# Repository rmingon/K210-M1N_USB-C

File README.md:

# K210-M1N USB-C Adapter

This repository contains the KiCad 9 project for a compact adapter board that breaks out the **Kendryte K210 M1n** M.2 (Key‑B) module to USB and a minimal set of GPIOs. The board’s USB‑C port is intended primarily for power and UART-based programming through an onboard CH340C USB–serial bridge.

## Hardware Overview

- **Form factor** – Single board implementing the Amphenol MDT320B03001 Key‑B M.2 socket on the top side and a USB‑C receptacle on the edge for direct plug-in to a host.
- **Power** – USB VBUS feeds the CH340C (`+5V`) and is decoupled locally (C9). The board relies on the M1n module’s onboard regulators for `+3.3V` and `+1V8`.
- **USB–UART** – CH340C in SOIC‑16 package with `D+`/`D-` routed to the USB‑C connector and a BOOT/RESET autoprogramming network (R7 to BOOT, R8 to RESET).
- **Status LEDs** – Two LEDs (D1/D2) with current-limiting resistors (R3/R4) monitor `+5V` and `VBUS`.
- **Breakout signals** – Key M.2 pins (IO, SPI0, DVP, etc.) are accessible via the module connector. The schematic uses global labels (`IO4`, `IO5`, …) matching Kendryte’s numbering.

### Board visuals

## Programming Workflow

- The CH340C exposes a UART for flashing firmware onto the K210 module.
- `~RTS` is routed through R8 to the `RST` net (M.2 pad 10), while `~DTR` drives the `BOOT` net (M.2 pad 53) via R7 to automate the boot sequence used by Kendryte tooling.
- Connect the USB‑C port to your host PC, install CH340 drivers if needed, and use Kendryte’s flashing tools over the enumerated serial port.

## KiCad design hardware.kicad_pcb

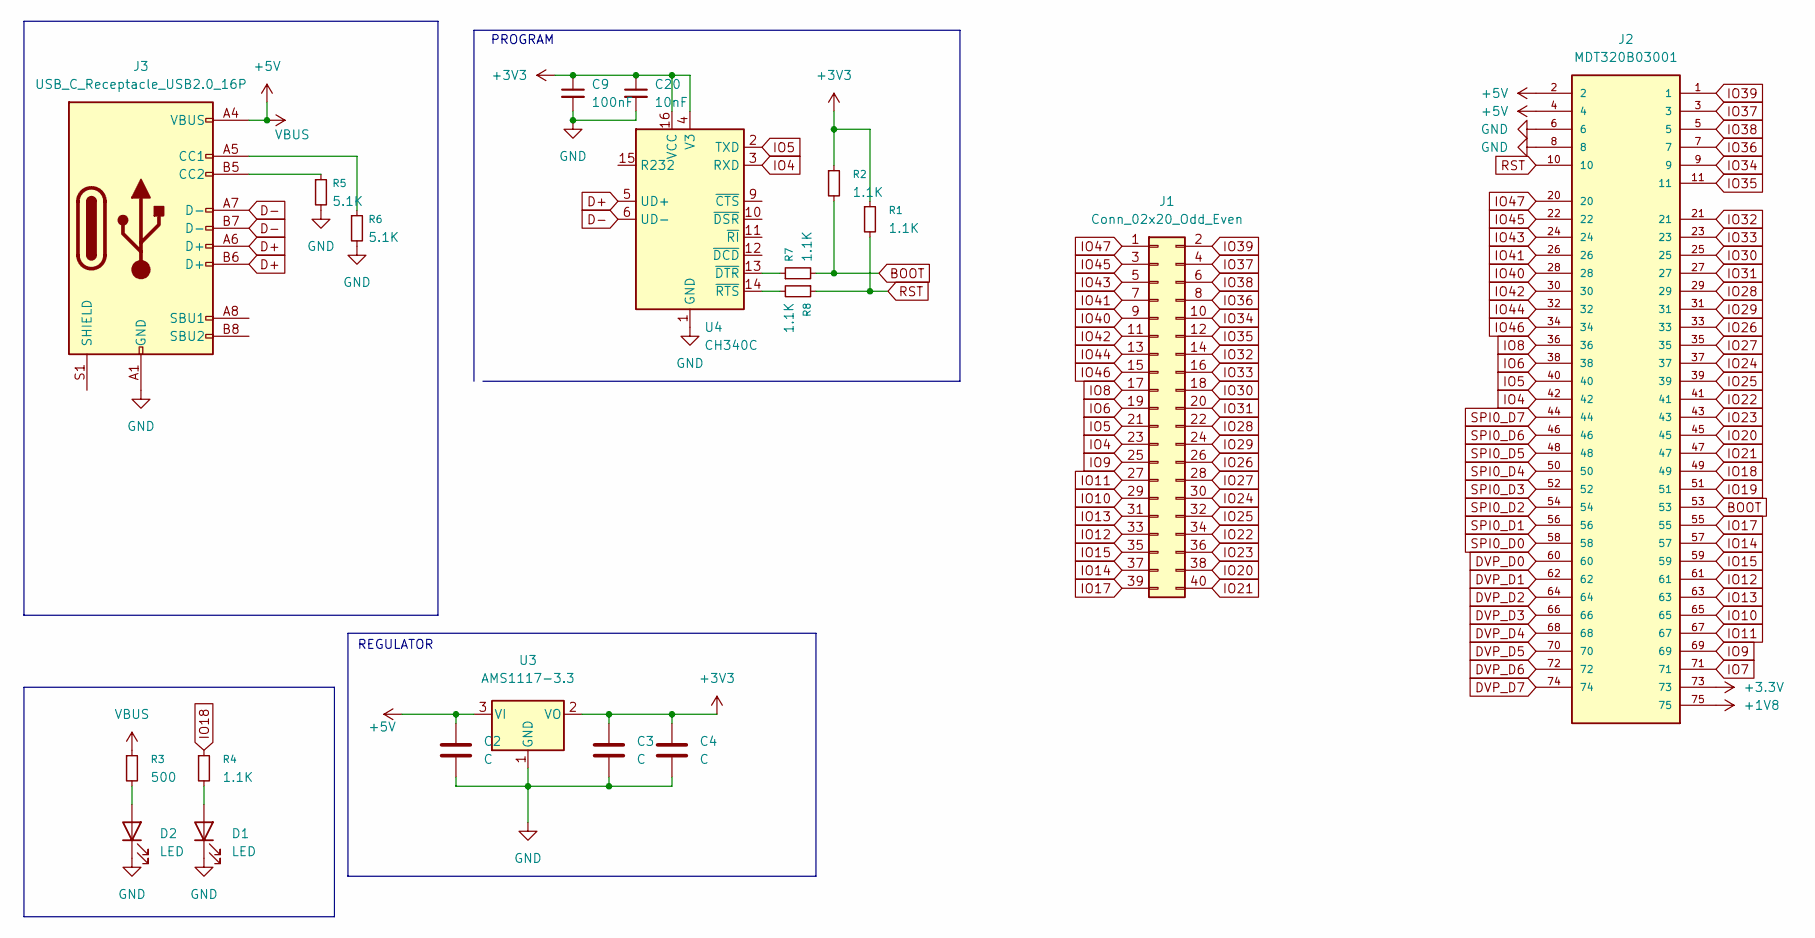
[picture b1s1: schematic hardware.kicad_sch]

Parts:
C2, C4: C; C_0603_1608Metric; LCSC C30926
C3: C; C_0603_1608Metric; LCSC C19702
C9: 100nF; C_0603_1608Metric
C20: 10nF; C_0603_1608Metric
D1, D2: LED; LED_0603_1608Metric
J1: Conn_02x20_Odd_Even; IDC-Header_2x20_P2.54mm_Horizontal
J2: MDT320B03001; AMPHENOL_MDT320B03001; PARTREV 4
J3: USB_C_Receptacle_USB2.0_16P
R1, R2, R4, R7, R8: 1.1K; R_0603_1608Metric
R3: 500; R_0603_1608Metric
R5, R6: 5.1K; R_0603_1608Metric
U3: AMS1117-3.3; SOT-223-3_TabPin2; LCSC C6186
U4: CH340C; SOIC-16_3.9x9.9mm_P1.27mm

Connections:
+1V8: J2.75
+3.3V: J2.73
+3V3: C3.1, C4.1, C9.1, C20.1, R1.1, R2.1, U3.2 (VO), U4.4 (V3), U4.16 (VCC)
+5V: C2.1, J2.2, J2.4, J3.A4 (VBUS), J3.A9 (VBUS), J3.B4 (VBUS), J3.B9 (VBUS), R3.1, U3.3 (VI)
BOOT: J2.53, R2.2, R7.2
D+: J3.A6 (D+), J3.B6 (D+), U4.5 (UD+)
D-: J3.A7 (D-), J3.B7 (D-), U4.6 (UD-)
DVP_D0: J2.60
DVP_D1: J2.62
DVP_D2: J2.64
DVP_D3: J2.66
DVP_D4: J2.68
DVP_D5: J2.70
DVP_D6: J2.72
DVP_D7: J2.74
GND: C2.2, C3.2, C4.2, C9.2, C20.2, D1.1 (K), D2.1 (K), J2.6, J2.8, J3.A1 (GND), J3.A12 (GND), J3.B1 (GND), J3.B12 (GND), R5.2, R6.2, U3.1 (GND), U4.1 (GND)
IO4: J1.23, J2.42, U4.3 (RXD)
IO5: J1.21, J2.40, U4.2 (TXD)
IO6: J1.19, J2.38
IO7: J2.71
IO8: J1.17, J2.36
IO9: J1.25, J2.69
IO10: J1.29, J2.65
IO11: J1.27, J2.67
IO12: J1.33, J2.61
IO13: J1.31, J2.63
IO14: J1.37, J2.57
IO15: J1.35, J2.59
IO17: J1.39, J2.55
IO18: J2.49, R4.1
IO19: J2.51
IO20: J1.38, J2.45
IO21: J1.40, J2.47
IO22: J1.34, J2.41
IO23: J1.36, J2.43
IO24: J1.30, J2.37
IO25: J1.32, J2.39
IO26: J1.26, J2.33
IO27: J1.28, J2.35
IO28: J1.22, J2.29
IO29: J1.24, J2.31
IO30: J1.18, J2.25
IO31: J1.20, J2.27
IO32: J1.14, J2.21
IO33: J1.16, J2.23
IO34: J1.10, J2.9
IO35: J1.12, J2.11
IO36: J1.8, J2.7
IO37: J1.4, J2.3
IO38: J1.6, J2.5
IO39: J1.2, J2.1
IO40: J1.9, J2.28
IO41: J1.7, J2.26
IO42: J1.11, J2.30
IO43: J1.5, J2.24
IO44: J1.13, J2.32
IO45: J1.3, J2.22
IO46: J1.15, J2.34
IO47: J1.1, J2.20
unnamed: D1.2 (A), R4.2
unnamed: D2.2 (A), R3.2
unnamed: J3.A5 (CC1), R6.1
unnamed: J3.B5 (CC2), R5.1
unnamed: R7.1, U4.13 (~DTR)
unnamed: R8.2, U4.14 (~RTS)
RST: J2.10, R1.2, R8.1
SPI0_D0: J2.58
SPI0_D1: J2.56
SPI0_D2: J2.54
SPI0_D3: J2.52
SPI0_D4: J2.50
SPI0_D5: J2.48
SPI0_D6: J2.46
SPI0_D7: J2.44

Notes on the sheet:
PROGRAM
REGULATOR

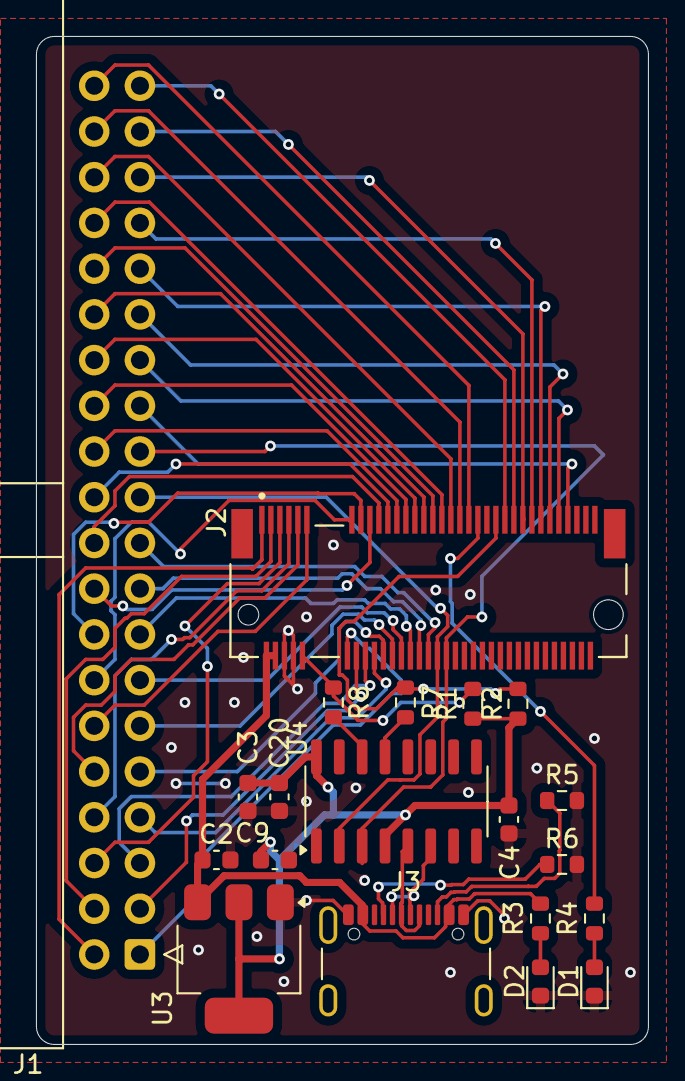
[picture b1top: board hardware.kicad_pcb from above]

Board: 2 copper layers, 34.0 x 56.0 mm, 20 parts (0 on the bottom side), 54 nets.

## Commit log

2025-11-01 add wiring + pcb
2025-11-01 add pictures
2025-11-01 switch uart wiring
2025-11-01 add readme
2025-11-06 add testing header
2025-11-06 add rst/boot pull up
2025-11-22 fix usb c wiring
